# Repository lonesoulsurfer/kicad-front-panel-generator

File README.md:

# KiCad Front Panel Generator

Panel Generator makes a front panel PCB from your KiCad PCB.

**[⬇ Download Panel Generator for Windows](https://github.com/lonesoulsurfer/kicad-front-panel-generator/releases/latest)**: on that page, under **Assets**, click **`PanelGenerator-v…-windows.zip`**.
⚠️ **Do not use the green *Code → Download ZIP* button.** That zip has only the source code. It does not have the app (`PanelGenerator.exe`).

Panel Generator is free. If it saves you time, you can [sponsor its work](https://github.com/sponsors/lonesoulsurfer).

Panel Generator finds each pot, jack, switch, LED and screen on your board. It cuts a hole of the correct size in the correct position for each part. You can add labels, shapes, pictures and artwork. A live preview shows the panel while you work. When the panel is correct, Panel Generator makes the gerbers for the PCB manufacturer. It also makes standard Eurorack panels (2HP to 42HP).

You do not have to copy the parts onto a User layer. You do not have to export to Fusion 360 or Inkscape and back. You do not have to draw the panel again by hand.

**▶ Watch the video: [Front Panel Design - Made Easy!](https://youtu.be/l9CzSfH8hN0)**

*The front panel for my Game of Life synth, in KiCad's 3D viewer. Panel Generator made all of it: the holes, labels, pot scales, boxes round the key functions and the glider. I did not use Inkscape.*

## What you need

- **Windows.** To use the source code on macOS or Linux, see the [technical guide](docs/TECHNICAL.md#run-from-source-windows-macos-linux).
- **KiCad 9 or 10.**
- **[Inkscape](https://inkscape.org) 1.2 or later.** You need it only if you draw your own artwork.

## Install

1. **[Download Panel Generator](https://github.com/lonesoulsurfer/kicad-front-panel-generator/releases/latest).** Under **Assets**, click **`PanelGenerator-v…-windows.zip`**. Do not click *Source code*.
2. Unzip the file into a folder of your choice.
3. Open the `PanelGenerator` folder and double-click **`PanelGenerator.exe`**.
4. Windows can show *"Windows protected your PC"* the first time. Click **More info**, then **Run anyway**. This message shows because the app does not have a paid signature certificate.
5. *(Optional)* Add the **Open Panel Generator** button to KiCad. See [Open it from KiCad](#open-it-from-kicad).
6. *(Optional)* Add the two footprint libraries to KiCad:
   1. In KiCad, click **Preferences → Manage Footprint Libraries**.
   2. Click the **Global Libraries** tab, then the folder icon.
   3. Add `PanelParts.pretty` from the Panel Generator folder. It has extra panel holes, for example jacks and screws.
   4. Add `Eurorack.pretty`. It has the Eurorack templates.

### Open it from KiCad

Panel Generator can add an **Open Panel Generator** button to the KiCad PCB editor. When you click the button, Panel Generator opens with the board that is open in KiCad. The button operates in KiCad 7, 8, 9 and 10.

1. In Panel Generator, click **＋ Add an "Open Panel Generator" button to KiCad**. This line is at the top left, below the name of your PCB.
2. Close the KiCad PCB editor.
3. Open the PCB editor again. The button is at the right end of the top toolbar. Its icon is a dark panel with a knob, a jack and an orange LED.

Panel Generator reads the PCB file that is saved on the disk. Save the board in KiCad before you click the button. Each time you save in KiCad, Panel Generator updates the panel.

If you move the Panel Generator folder, run `PanelGenerator.exe` one time from the new folder. The button then finds the app again.

<details><summary>Other ways to install the button (KiCad Plugin and Content Manager)</summary>

**From a file:**
1. In KiCad, open the **Plugin and Content Manager**.
2. Click **Install from File…**.
3. Click `KiCad-button-plugin.zip` in the Panel Generator folder one time, then click **Open**. Do not double-click the file.
4. Click **Apply Pending Changes**.

**From the list of this project:**
1. In the Plugin and Content Manager, click **Manage…**, then **+**.
2. Paste `https://raw.githubusercontent.com/lonesoulsurfer/kicad-front-panel-generator/main/pcm/repository.json` and click **Save**.
3. At the top, select *Panel Generator (lonesoulsurfer)*.
4. Click **Install** on **Panel Generator button**.
5. Click **Apply Pending Changes**.

With this method, KiCad shows new versions of the button automatically.

If you install the button with two methods, KiCad shows only one button.
</details>

## How to use it

### 1. Select your PCB

1. Save your board in KiCad.
2. In Panel Generator, click **Browse…**.
3. Select the `.kicad_pcb` file.

The preview shows a front panel with the same shape as your PCB. It has holes for all the parts that need them, for example pots, LEDs, audio jacks, switches and screens.

Panel Generator reads only the saved `.kicad_pcb` file. When you move a part, save the board in KiCad again. The preview then updates automatically. The list at the top keeps the boards that you used before. Select a board from this list to open it again.

### 2. Set the size, corners and holes

The settings are on two tabs:
- **Panel**: the board itself (size, shape and holes).
- **Artwork**: all that is printed on the panel.

Click the heading of a section to close it or to open it. Some sections have a switch in the heading. Use the switch to turn the section on or off.

The panel starts with the same size as your PCB. On the **Panel** tab, you can set these items:

- **Extra round the PCB**: makes the panel larger on all sides, for example to fit a case. To set a different value for each side, select *Set each side separately*.
- **Corner radius**: makes the corners round. 0 gives square corners.
- **Case mounting holes**: screw holes to attach the panel to your case. You can put them in the corners, or in the corners and at the middle of each side. Set the hole size and the distance from the hole centre to the edge. The line below shows how much panel material stays between the hole and the edge. Select **Slots** to make slots, not round holes. Slots let you adjust the position of the panel.
- **Screw heads**: a screw head is wider than its hole. Text near a mounting hole can go under the screw head. Panel Generator shows a dotted circle with the size of the head round each screw hole. This includes the mounting holes of the PCB, the case holes, and the screw holes of parts such as screens. If something printed is under a head, it shows in orange, and Result gives a warning.
   - *Auto* makes the head two times the hole size. This is approximately correct for pan-head screws.
   - Select your screw from the list, or select *Your own size…* and type the size. The list keeps the sizes that you type.
   - Or drag the edge of a dotted circle in the preview. The circle becomes bright when the pointer is on its edge. The size shows while you drag. When you release the mouse button, all the screw heads change to that size.
   - Select *Off* to remove the circles.

Each change shows in the preview immediately.

**To use the preview:**
- Turn the **mouse wheel** to zoom.
- Drag with the **right mouse button** to move the view.
- Click **Fit** to see all of the panel.
- Put the pointer on a hole to see its part and its size.
- To make the preview larger, drag the bar between the settings and the preview. You can also drag the bar above the buttons and the Result box.

**Extra holes** are for parts that are not on the PCB. Examples are a window, or a jack or a switch with wires to the board.

- **To add a hole:**
   1. Select a **Hole size** from the list. Or select *Your own size…* and type the size. The list keeps the sizes that you type.
   2. Click **Hole**.
   3. Click the panel where the hole goes.

   **Rectangle** and **Slot** operate in the same way. You can also right-click the panel and add a hole at that position.
- **Alignment:** a new hole moves into line with the other holes. If there is no hole to align with, it goes to the nearest 0.5 mm. To put it in a free position, hold **Alt**. To stop all alignment, clear the **Snap** check box above the preview.
- **Small movements:** click the hole, then push the **arrow keys**. Each push moves it 0.1 mm. With Shift, each push moves it 1 mm.
- **Exact values:** click the hole. Its settings show on the left: the distance from its centre to the **left edge** and to the **top edge** of the panel, and its size. Type exact values there. For a round hole, select a new **Hole size** from the list to change its size. You can also drag one of its white corner squares. A rectangle shows its width and height while you drag.
- **Many holes at the same time:** drag a box round the holes that you added, or Shift-click each hole. Then you can drag them together, **line them up** in a row or column, or type the **spacing** (centre to centre).
- **Copy** (Ctrl+D) adds a copy of the selected holes, with the same sizes and spacing. Two holes in a row become four holes with equal spacing. Drag the copy to a different position if necessary. Push **Delete** to remove the selected holes.
- **Part sizes:** right-click a hole and select *Show the part's size round it*. A dashed blue circle or rectangle shows the real size of the part, for example the nut of a jack or a knob. Use it to set the space between the holes.
   - Drag an edge to change the size. The size and the gap to the nearest part show while you drag.
   - A side of a rectangle moves alone. Thus the rectangle can extend to one side of its hole, for example for a USB board with the connector at one end.
   - Drag a corner to move two sides.
   - Hold **Shift** to keep the rectangle equal on all sides of the hole.
   - Panel Generator does not cut or print these guides.
- **Measure** (above the preview) is a ruler. Click two points to see the distance between them. The ruler snaps to the centres and edges of holes and to the panel edges. Hold **Ctrl** to keep it horizontal or vertical.
- **The ruler is also a guide.** After the first click, type a length (for example `16`) and push Enter. The second end goes exactly that distance away. The ruler stays on the panel until you click **Clear ruler**. All that you drag, add or paste snaps to its ends and its centre.

   *Example:* you need two holes 16 mm apart, with a slot between them.
   1. Add the first hole.
   2. Measure 16 mm from its centre.
   3. Paste a second hole on the far end of the ruler.
   4. Put the rectangle on the centre of the ruler.

Panel Generator checks the extra holes in the same way as all other holes: too near an edge, or on top of a part. If you make the panel larger later, the extra holes stay in the same position relative to the PCB.

**The colours in the preview:**

- **Orange outline:** a hole is very near the panel edge or another hole. The material there can be too thin.
- **Red outline:** a real problem, for example two holes on top of each other.
- **Orange dashed box:** a part that possibly needs a hole, but has no hole. If it does not need a hole (for example a tactile switch behind the panel), click it in the preview. Panel Generator then does not show it again. If it needs a hole, see the [technical guide](docs/TECHNICAL.md).

The **Result** box below the preview shows all the items that you must check.

### 3. Add labels (optional)

1. On the **Artwork** tab, open **Labels**.
2. Select *A name next to each control*.

Each pot, jack and switch gets a name next to its hole, in the silkscreen of the panel. The name comes from the PCB. If the part has a `Label` field, Panel Generator uses it. If not, it uses the Value of the part. For example, a pot with the Value `Cutoff` gets the label CUTOFF.

- Select **above** or **below** the holes, and set the **gap** between the label and the hole.
- Set the **text size** and the **font**. Turn **bold** and **ALL CAPS** on or off.
- Click **Edit labels…** to see all the labels in a list. In the list, you can change the text, or hide a label.
- To change one label, right-click it and select **Change text…**.

### 4. Make the artwork automatically (optional)

The **Artwork** tab can draw the artwork for your panel. You do not have to use Inkscape. Select a **Style** at the top. Then change the items in the sections below it: Title, Labels, Pots, Shapes, Border, Lines and Pictures.

- **Pot scales:** tick marks, the numbers 0 to 10, or a centre-zero scale (− 0 +) round each pot, for a 300° turn. Set the **Knob** size, so that the scale and the label start outside the knob.
- **Shapes round a hole:**
   1. Under **Shapes**, set the shape (circle, box, triangle, hexagon or diamond), filled or outline, gap, line thickness and corners.
   2. Right-click a hole and select *Add a shape round it*.

   Each new shape gets these settings, so a row of shapes is quick to make. The gap is the distance from the hole to the inner side of the line. A thicker line grows outwards. To change a shape, click it. The same settings then change that shape. You can also drag its edges. If you pull a filled box over a label, the label is cut out of the box. You can put a shape round all holes, also the holes that the automatic options below do not find.
- **Rings** round push buttons. Set the thickness of the ring and its gap from the hole.
- **Vertical outputs in filled boxes:** some jacks come up through the panel and have OUT in their label. Each of these jacks gets a filled box, with the label cut out. This is the usual output marking on modular panels. These also get a box:
   - a jack with your own text OUT next to it.
   - a round extra hole with the text OUT next to it (a jack with wires that is not on the PCB).
- **Boxes round rows of controls:** select *Box* under Pots, Buttons or Jacks. Panel Generator puts a box round each row or column of 3 or more controls, with the scales and labels in the box. Drag the top, the bottom or a side of the box to change its size. The opposite side moves too, so the box stays centred.
- **Horizontal jacks in tabs:** some jacks lie flat at the panel edge, and the plug goes in from the side. These jacks get a filled tab at the edge, with the labels cut out. Labels such as MIDI IN and MIDI OUT become IN and OUT, with MIDI below them. Drag an edge of a tab or an output box to make it larger. It snaps to the edges of the other tabs and boxes, so you can make them all the same size.
- **Border:** a line round the panel. It can be square, follow the panel corners, or have its own corner radius. Set its **gap from the edge** and its **thickness**. If the gap is 0, Panel Generator sets it automatically: 1.5 mm, or just inside the case holes.
- **Title:** your title, and your name or brand in small text along the bottom. The title can go across the top, letter below letter down a side, or turned on its side (reading up or reading down). Select **Mirror image** to flip the letters left to right. The title goes in the first free position. Drag it to a different position if necessary. If there is no free position, the title shows on top of something, and Result gives a warning. Drag the title to a clear area.
- **Copies of the title:** click the title, push **Ctrl+C**, then **Ctrl+V**. Each copy has its own position, size and direction.

The styles are *None*, *Minimal*, *Classic synth* and *Modular*. If you change a setting, the style becomes *Custom*. When the panel looks correct, click **Save this look as my style**. Each new PCB then starts with the same fonts, sizes, scales, rings and border, and *My style* shows in the Style list.

To change the artwork of one part, click its **Artwork** cell in **Edit labels**. For example, use this for a centre-zero scale on a pan pot, or for an output jack that does not have OUT in its label.

If an item touches a hole, a label or the edge, Panel Generator does not include it, and Result gives a note.

You can use this artwork and Inkscape together. The artwork that Panel Generator makes shows in the Inkscape file on its own layer, and you can draw more on top of it.

### 5. Add your own text, pictures and boxes (optional)

You do this work in the preview. Your own texts are under **Labels**, and pictures are under **Pictures**. To remove them from the panel but keep them, clear *My own texts on the panel*, or turn Pictures off. For example, do this when you use Inkscape artwork that has its own text.

- **To move an item, drag it.** You can drag a label, your text, a picture, a line or the title. It snaps to:
   - the line of the other labels.
   - the centre of holes.
   - the centre of each key below a window or in a merged slot. A blue dotted outline with a cross at its centre shows each key.
   - the point half way between two holes (for example a MIDI label above its IN and OUT jacks).
   - the centre of the gap between two items.

   Hold **Alt** to put the item in a free position. For small movements, click the item and push the arrow keys (0.1 mm, or 1 mm with Shift).
- **To change an item, click it.** Its settings show on the left: text, size, position and delete. To change the size of the title, a picture or one of your texts, click it and drag one of its white corner squares.
- **To add text:** under **Labels → Your own**, click **Text…**. Or right-click the panel and select *Add text here*. Then click where the text goes, and type it. Use this for items that are not on the PCB, for example the function of each key.
- **Boxes round text:** use a box for a key with two functions, or for a function that needs two keys.
   1. Click the text.
   2. Set **Box** to *Line round it* or *Filled bar*. A filled bar has the text cut out.
   3. Drag the ends of the box to extend it over the keys. The ends snap to the key labels, to the edges of holes and to other boxes.

   If you extend the box over other texts, they go into the box at their positions. Thus you can make one long bar below a row of keys. If the two ends of the box are equal, they move together. If one end is longer, or one end snaps to an edge, only the end that you pull moves. Hold **Shift** to move only one end.
- **Lines:**
   1. Under **Lines**, click **Line**.
   2. Click where the line starts, then where it ends. Hold **Ctrl** to keep it horizontal or vertical.

   Use lines as dividers, brackets or signal-flow arrows. Click a line to change its **Thickness**, to add an arrowhead, or to type its exact length. Drag an end to move that end. A line that ends at a hole goes to the edge of the hole.
- **Pictures:** click **Picture…** and select a PNG, JPG, GIF, BMP or SVG file (for example a logo). The dark parts print. Drag the picture into position. Click it to set its width, turn it, print the light parts, or delete it.
- **Many items at the same time:** drag a box round them, or Shift-click each item. You can select labels, texts, lines, pictures and extra holes together. Then you can drag, copy or delete them together.
- **Delete:** push the **Delete** key to remove the selected item.
   - A PCB label is hidden, not deleted. **Edit labels** shows it again.
   - On a box round text, Delete removes only the box. The text stays.
   - You can also delete a box that Panel Generator made (round an output, an edge tab or a row of pots). To show these boxes again, right-click the panel and select *Bring back deleted boxes*.
   - On the title or the maker name, Delete removes the text.
- **Copy and paste:** select a text, a picture, a line, the title or extra holes. Push **Ctrl+C**, then **Ctrl+V**. The copy goes to the position of the pointer. Or right-click the panel and select *Paste here*. A copied PCB label becomes one of your own texts.
- **Reset** (next to Undo) starts the panel again from your PCB. The panel gets the size of the PCB, with its holes and nothing else. This also removes the parts and cutouts that you put into the panel file in KiCad. Panel Generator asks before it does this. When you generate again, it keeps the old panel file as a backup (`…_panel.before-reset.kicad_pcb`). Undo brings it all back.
- **Undo** (or Ctrl+Z) cancels the last change. This can be a setting on the left or an action in the preview. You can undo up to 50 changes.

### 6. Draw your own artwork in Inkscape (optional)

Use Inkscape for artwork that Panel Generator does not make, for example a complex logo or your own drawings.

1. Turn on **Artwork from Inkscape**.
2. Click **Create artwork file**.

Panel Generator saves an Inkscape file in the `Front Panel` folder and opens it. The Inkscape page is an exact 1:1 copy of your panel. Each hole shows in red, so you can see where to put the artwork. To align your artwork with the red holes, use **Align and Distribute** in Inkscape.

- Draw on the **Artwork** layer. Do not move the page, and do not change its size.
- **Black** prints on the panel as silkscreen.
- **White** cuts out of black. Thus white text on a black bar becomes text cut into the bar.
- **Save** in Inkscape. Panel Generator reads the file automatically, and the preview shows your artwork. You can change and save it as many times as necessary.
- **If you move a part on the PCB:** when you save the PCB, the red holes in the artwork file update automatically. Inkscape does not see this change. When Panel Generator shows *Guides updated*, save your artwork in Inkscape. Then click **File → Revert** in Inkscape to see the new positions.
- **Do not draw on the red layer.** When you click a red hole to align something, Inkscape can change to the red layer. If you draw on the red layer, Panel Generator moves that item to the top of your Artwork layer, and gives a note. (Use **File → Revert** in Inkscape to see it.) To put one item on top of another, use Home or Page Up. Do not make a new layer.

Panel Generator does not print the red holes. It draws them again from the PCB each time you generate. Thus they always agree with the board.

### 7. Generate the panel

When the preview is correct, click **Generate panel**. Panel Generator makes the panel file (`<your board>_panel.kicad_pcb`) in a `Front Panel` folder next to your PCB. Then it opens the file in KiCad, so you can check it, also in the 3D viewer.

Panel Generator saves your settings and all your work in the preview while you work. You can close the window at any time. Later, you can change the PCB, the settings or the artwork. The status line next to the buttons then tells you that the panel is out of date. Click **Generate panel** again to update it.

Close the panel file in KiCad before you generate again. If the file is open, Panel Generator cannot replace it.

### 8. Make gerbers

Click **Make gerbers**. Panel Generator uses KiCad to make the gerber and drill files. It checks the panel and puts all the files in one zip file in the `Front Panel` folder. Upload that zip file to JLCPCB, PCBWay or a different PCB manufacturer.

Order it as a usual 1.6 mm PCB. Black solder mask with white silkscreen gives the classic synth panel appearance.

**3D printing or CNC:** the panel file is a usual KiCad PCB. To get a 3D model, open it in KiCad and use **File → Export → STEP**. To get the outline and holes for a CNC machine, click **File → Plot**, select the DXF format and the Edge.Cuts layer, and plot.

## Eurorack

1. Start a new PCB in KiCad.
2. Push **A** and find the template for your size in `Eurorack.pretty` (for example `Eurorack_8HP`).
3. Put the template on the board at 0 degrees. The template draws the PCB outline, the panel outline, and the top and bottom rail areas. The rail areas show where you cannot put parts.
4. Put your pots, jacks and LEDs inside the PCB outline.
5. Save the board, and open it in Panel Generator.

Panel Generator finds the template. It makes a standard Eurorack panel, 128.5 mm tall, with the correct width for that HP. It puts the rail holes in the standard positions: 2 holes up to 9HP, and 4 holes from 10HP. You can change the rail holes to slots. If a part goes into a rail area, it shows in red, so you can move it before you order.

## Try it

[`examples/demo_synth`](examples/demo_synth) is a small synth board with 4 pots, 2 jacks, an LED and 8 keys. It uses the standard KiCad footprints. Open it in Panel Generator to try all the functions before you use your own board.

## More information

The **[technical guide](docs/TECHNICAL.md)** gives all the other information:
- the command line.
- how Panel Generator calculates the size of each cutout, and how to add your own parts in `panel_rules.json`.
- cutouts that you draw on the User.1 layer.
- parts for the panel only, and part markers.
- how to remove a hole or change its size.
- all the checks.

## Support the project

Panel Generator is free for non-commercial use. I make it in my free time. If it helps you, you can support its work:

- **[Sponsor me on GitHub](https://github.com/sponsors/lonesoulsurfer).** You can give one time or each month. GitHub takes no fee.
- **Tell other people.** Show your panels, and put a link to this page in your project.
- **Report problems.** Open an issue, and attach the PCB file if possible.

## Licence

**Panel Generator is free for non-commercial use**, under the [PolyForm Noncommercial License 1.0.0](LICENSE).

**You can sell the panels that you make with it**, for your own synths, kits and modules. This is also permitted for a business.

You must have a commercial licence to sell the tool, or to get money for its use on the designs of other persons. To ask for a commercial licence, open an issue with the title *Commercial licence*.

[LICENSING.md](LICENSING.md) gives the details in plain words.

Versions 0.26.0 and earlier have the MIT licence. The KiCad button plugin (the `kicad-plugin` folder) also has the MIT licence.

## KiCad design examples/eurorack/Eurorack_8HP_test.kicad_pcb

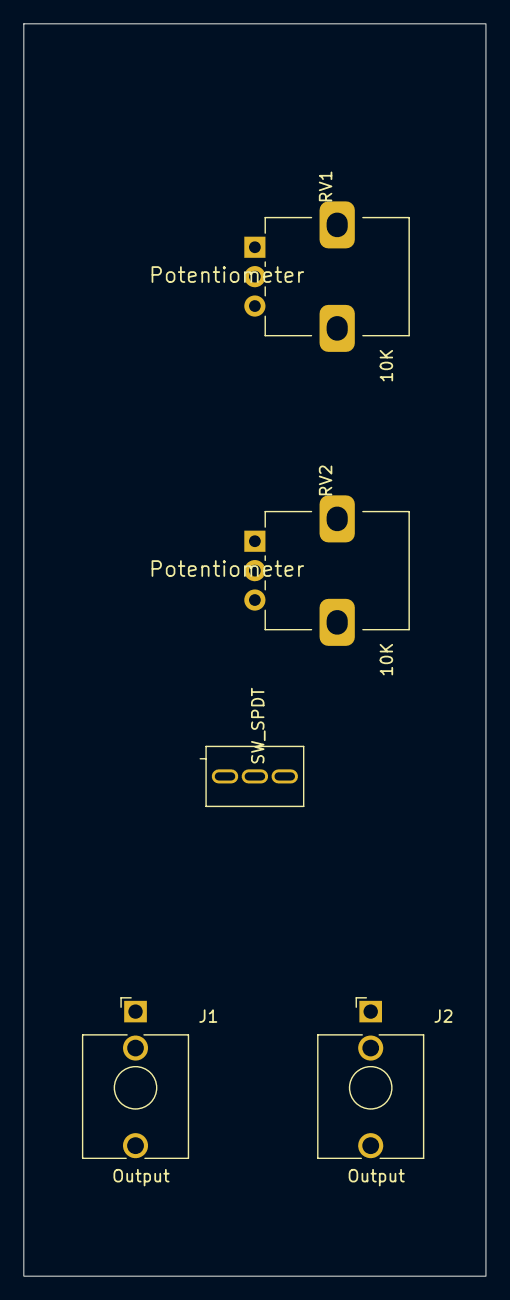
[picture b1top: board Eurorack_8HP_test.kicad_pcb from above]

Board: 2 copper layers, 39.3 x 106.5 mm, 6 parts (0 on the bottom side), 4 nets, no tracks yet.

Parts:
J1, J2: Output; Jack_3.5mm_QingPu_WQP-PJ398SM_Vertical_CircularHoles
PNL1: Eurorack_8HP
RV1, RV2: 10K; Potentiometer_Alps_RK09K_Single_Vertical
SW1: SW_SPDT; SW_SPDT_Toggle_QuarterInch_Bushing

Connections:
+3.3V: RV1.3, RV2.3
Cutoff: RV1.2, RV2.2
GND: J1.S, J2.S, RV1.1, RV2.1
unnamed: J1.T, J2.T
